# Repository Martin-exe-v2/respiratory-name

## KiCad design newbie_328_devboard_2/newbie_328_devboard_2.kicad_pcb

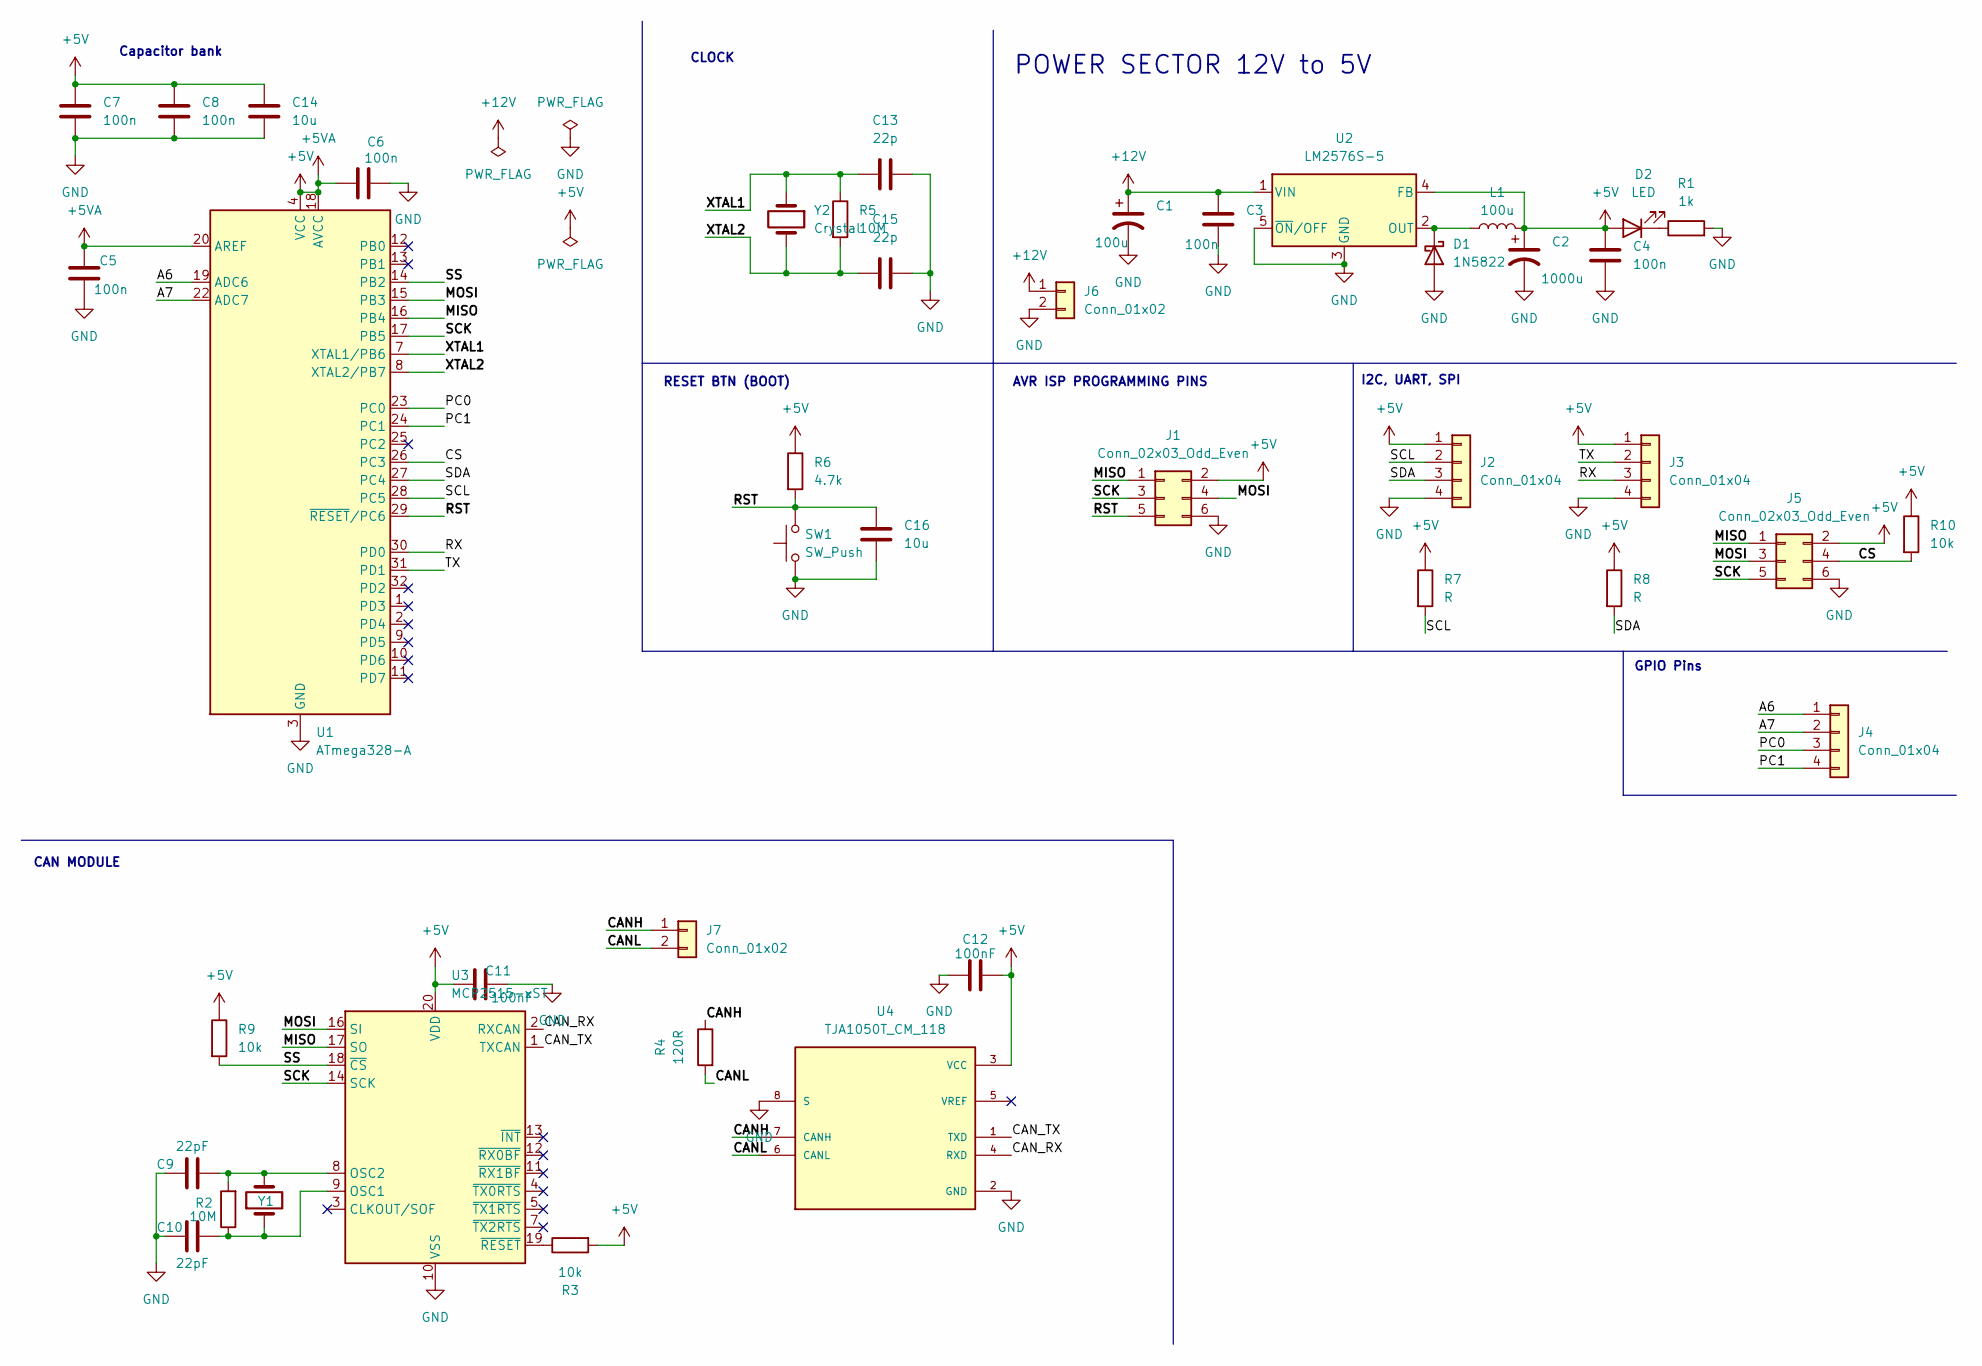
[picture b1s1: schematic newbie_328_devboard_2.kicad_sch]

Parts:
C1: 100u; CP_Radial_D10.0mm_P2.50mm
C2: 1000u; CP_Radial_D10.0mm_P2.50mm
C3, C4, C5, C6, C7, C8: 100n; C_0805_2012Metric_Pad1.18x1.45mm_HandSolder
C9, C10: 22pF; C_0805_2012Metric_Pad1.18x1.45mm_HandSolder
C11, C12: 100nF; C_0805_2012Metric_Pad1.18x1.45mm_HandSolder
C13, C15: 22p; C_0805_2012Metric_Pad1.18x1.45mm_HandSolder
C14, C16: 10u; C_0805_2012Metric_Pad1.18x1.45mm_HandSolder
D1: 1N5822; D_DO-201AD_P15.24mm_Horizontal
D2: LED; LED_0805_2012Metric_Pad1.15x1.40mm_HandSolder
J1, J5: Conn_02x03_Odd_Even; PinHeader_2x03_P2.54mm_Vertical
J2, J3, J4: Conn_01x04; PinHeader_1x04_P2.54mm_Vertical
J6, J7: Conn_01x02; PinHeader_1x02_P2.54mm_Vertical
L1: 100u; L_10.4x10.4_H4.8
R1: 1k; R_0805_2012Metric_Pad1.20x1.40mm_HandSolder
R2, R5: 10M; R_0805_2012Metric_Pad1.20x1.40mm_HandSolder
R3, R9, R10: 10k; R_0805_2012Metric_Pad1.20x1.40mm_HandSolder
R4: 120R; R_0805_2012Metric_Pad1.20x1.40mm_HandSolder
R6: 4.7k; R_0805_2012Metric_Pad1.20x1.40mm_HandSolder
R7, R8: R; R_0805_2012Metric_Pad1.20x1.40mm_HandSolder
SW1: SW_Push; SW_PUSH_6mm
U1: ATmega328-A; TQFP-32_7x7mm_P0.8mm
U2: LM2576S-5; TO-263-5_TabPin3
U3: MCP2515-xST; TSSOP-20_4.4x6.5mm_P0.65mm
U4: TJA1050T_CM_118; SOIC127P600X175-8N; PARTREV 4
Y1: 20MHz; Crystal_HC49-U_Vertical
Y2: Crystal; Crystal_HC49-U_Vertical

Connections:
+5V: C2.1, C4.1, C5.1, C6.1, C7.2, C8.2, C11.2, C12.2, C14.2, D2.2 (A), J1.2, J2.1, J3.1, J5.2, L1.2, R3.2, R6.1, R7.1, R8.1, R9.1, R10.1, U1.4 (VCC), U1.6 (VCC), U1.18 (AVCC), U1.20 (AREF), U2.4 (FB), U3.20 (VDD), U4.3 (VCC)
+12V: C1.1, C3.1, J6.1, U2.1 (VIN)
/A6: J4.1, U1.19 (ADC6)
/A7: J4.2, U1.22 (ADC7)
/CANH: J7.1, R4.1, U4.7 (CANH)
/CANL: J7.2, R4.2, U4.6 (CANL)
/CAN_RX: U3.2 (RXCAN), U4.4 (RXD)
/CAN_TX: U3.1 (TXCAN), U4.1 (TXD)
/CS: J5.4, R10.2, U1.26 (PC3)
/MISO: J1.1, J5.1, U1.16 (PB4), U3.17 (SO)
/MOSI: J1.4, J5.3, U1.15 (PB3), U3.16 (SI)
/PC0: J4.3, U1.23 (PC0)
/PC1: J4.4, U1.24 (PC1)
/RST: C16.1, J1.5, R6.2, SW1.2, U1.29 (~RESET/PC6)
/RX: J3.3, U1.30 (PD0)
/SCK: J1.3, J5.5, U1.17 (PB5), U3.14 (SCK)
/SCL: J2.2, R7.2, U1.28 (PC5)
/SDA: J2.3, R8.2, U1.27 (PC4)
/SS: R9.2, U1.14 (PB2), U3.18 (~CS)
/TX: J3.2, U1.31 (PD1)
/XTAL1: C13.1, R5.1, U1.7 (XTAL1/PB6), Y2.1
/XTAL2: C15.1, R5.2, U1.8 (XTAL2/PB7), Y2.2
GND: C1.2, C2.2, C3.2, C4.2, C5.2, C6.2, C7.1, C8.1, C9.1, C10.1, C11.1, C12.1, C13.2, C14.1, C15.2, C16.2, D1.2 (A), J1.6, J2.4, J3.4, J5.6, J6.2, R1.2, SW1.1, U1.3 (GND), U1.5 (GND), U1.21 (GND), U2.3 (GND), U2.5 (~ON/OFF), U3.10 (VSS), U4.2 (GND), U4.8 (S)
unnamed: D1.1 (K), L1.1, U2.2 (OUT)
unnamed: D2.1 (K), R1.1
unnamed: C10.2, R2.1, U3.9 (OSC1), Y1.1
unnamed: C9.2, R2.2, U3.8 (OSC2), Y1.2
unnamed: R3.1, U3.19 (~RESET)

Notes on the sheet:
POWER SECTOR 12V to 5V
Capacitor bank
RESET BTN (BOOT)
AVR ISP PROGRAMMING PINS
I2C, UART, SPI
CLOCK
CAN MODULE
GPIO Pins

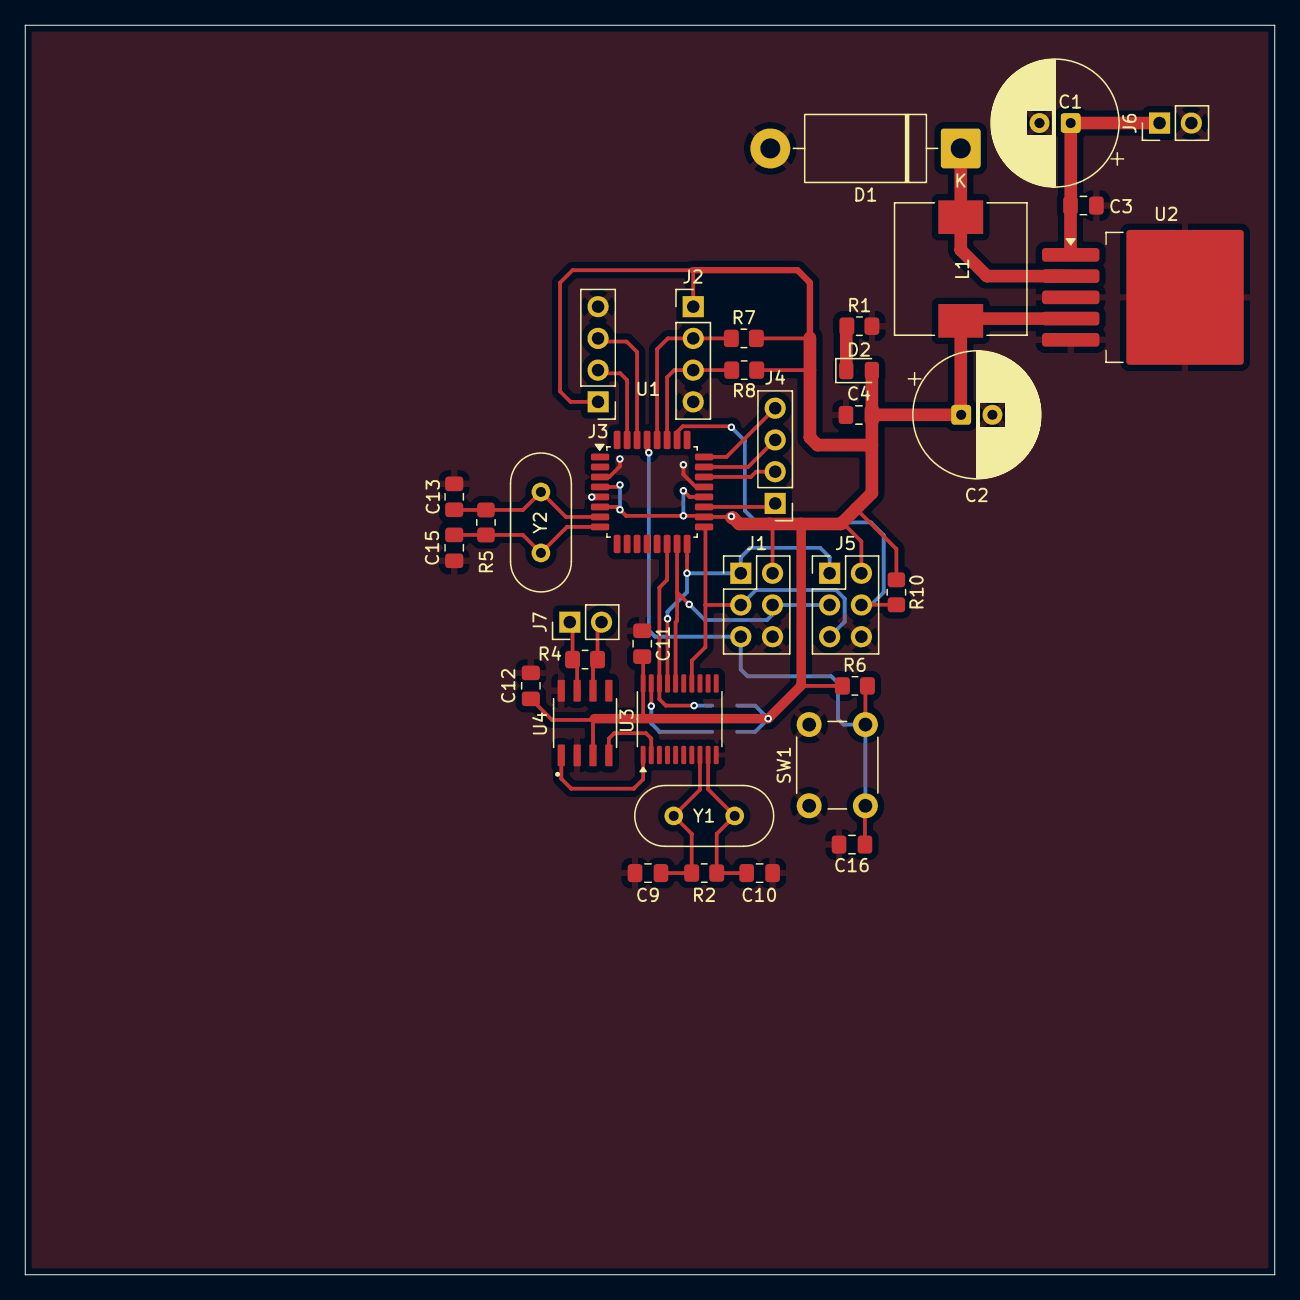
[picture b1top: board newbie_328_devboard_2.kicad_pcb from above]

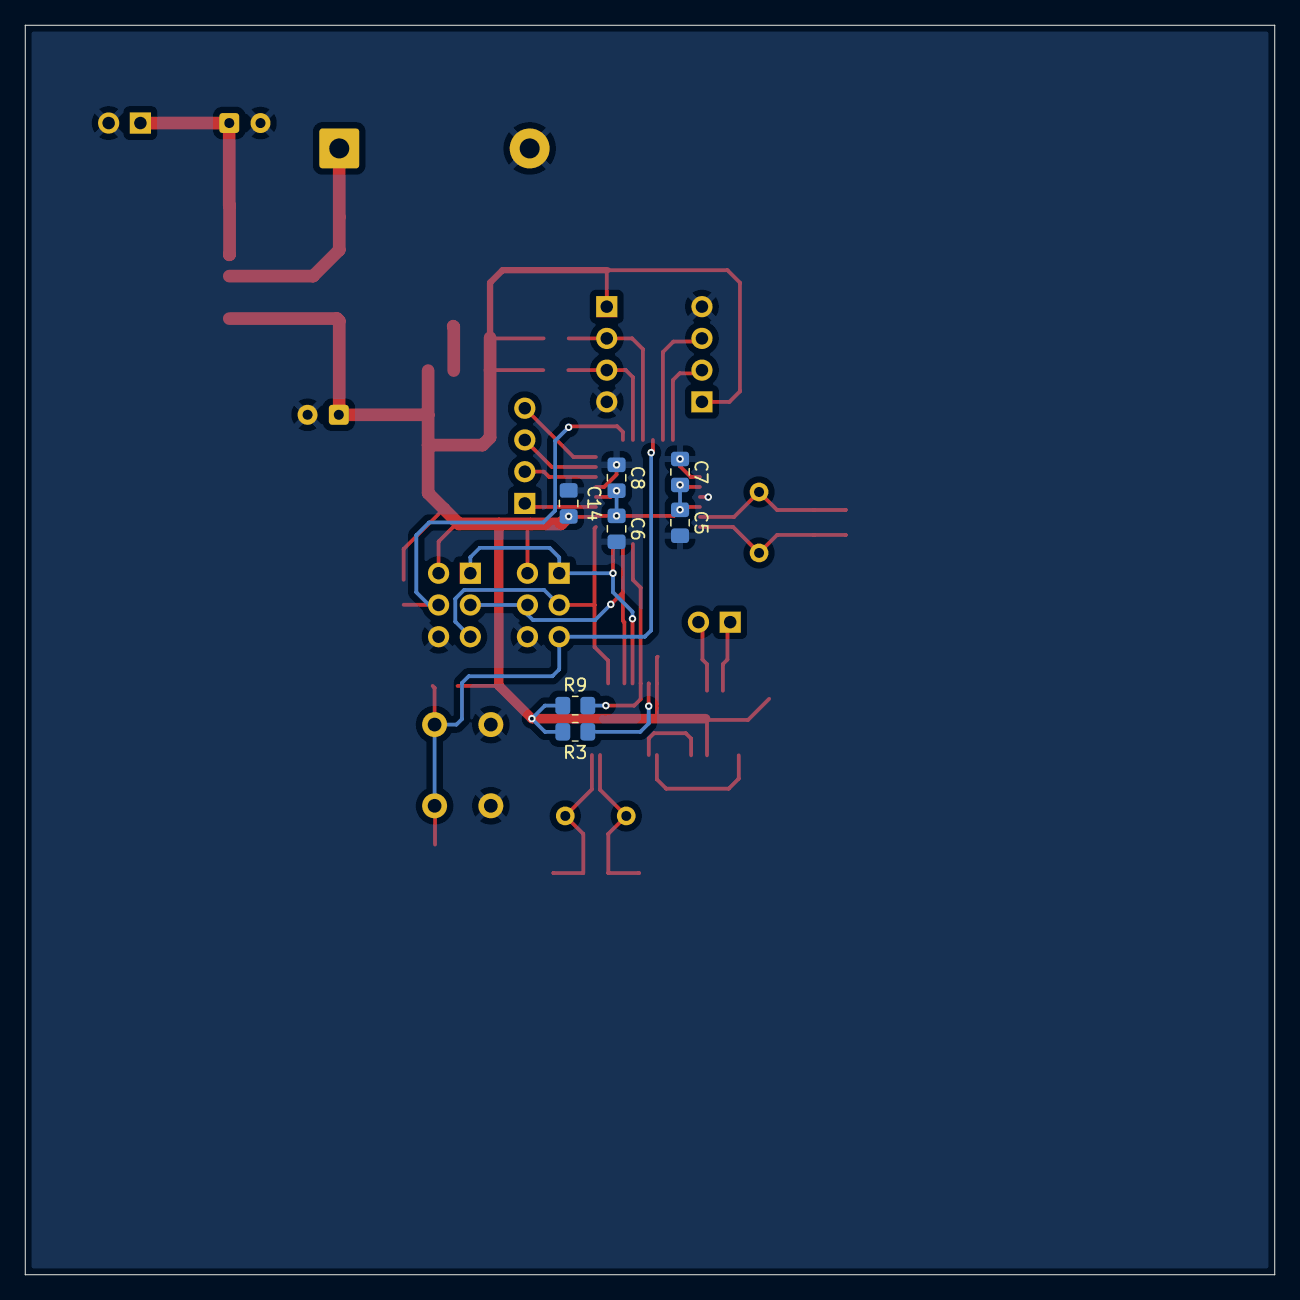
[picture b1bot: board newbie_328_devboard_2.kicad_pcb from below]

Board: 2 copper layers, 100.0 x 100.0 mm, 43 parts (7 on the bottom side), 28 nets.

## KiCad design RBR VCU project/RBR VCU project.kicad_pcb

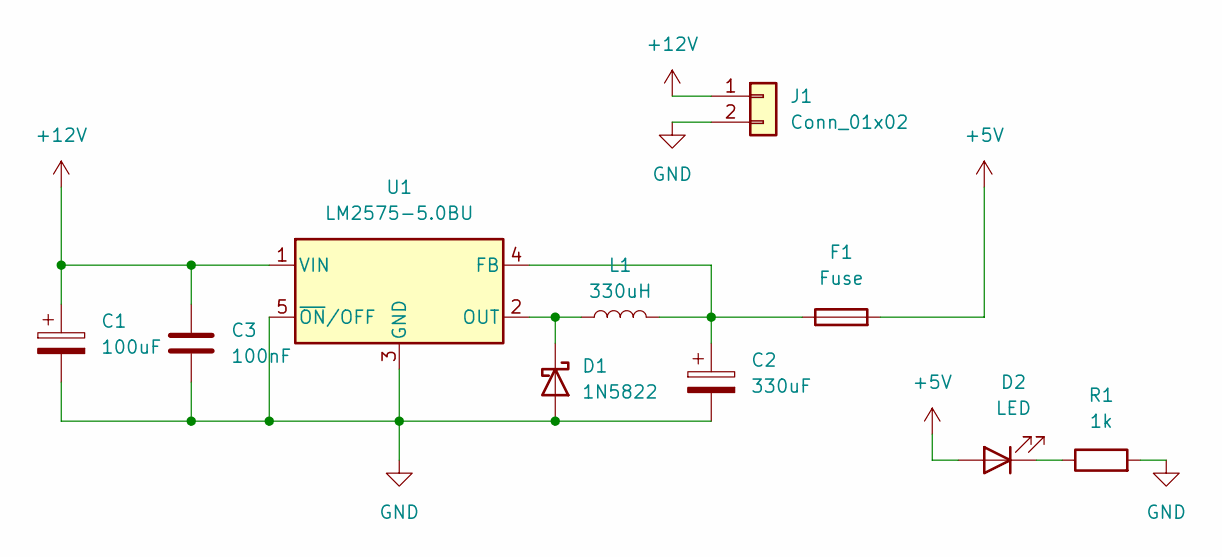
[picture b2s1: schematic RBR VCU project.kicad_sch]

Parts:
C1: 100uF; CP_Radial_D6.3mm_P2.50mm
C2: 330uF; CP_Radial_D6.3mm_P2.50mm
C3: 100nF; C_0805_2012Metric_Pad1.18x1.45mm_HandSolder
D1: 1N5822; D_DO-201AD_P15.24mm_Horizontal
D2: LED; D_0805_2012Metric_Pad1.15x1.40mm_HandSolder
F1: Fuse; Fuse_0805_2012Metric_Pad1.15x1.40mm_HandSolder
J1: Conn_01x02; JST_XH_B2B-XH-A_1x02_P2.50mm_Vertical
L1: 330uH; L_Neosid_SM-NE127_HandSoldering
R1: 1k; R_0805_2012Metric_Pad1.20x1.40mm_HandSolder
U1: LM2575-5.0BU; TO-263-5_TabPin3

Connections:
+5V: D2.2 (A), F1.2
+12V: C1.1, C3.1, J1.1, U1.1 (VIN)
GND: C1.2, C2.2, C3.2, D1.2 (A), J1.2, R1.2, U1.3 (GND), U1.5 (~ON/OFF)
unnamed: D1.1 (K), L1.1, U1.2 (OUT)
unnamed: D2.1 (K), R1.1
unnamed: C2.1, F1.1, L1.2, U1.4 (FB)

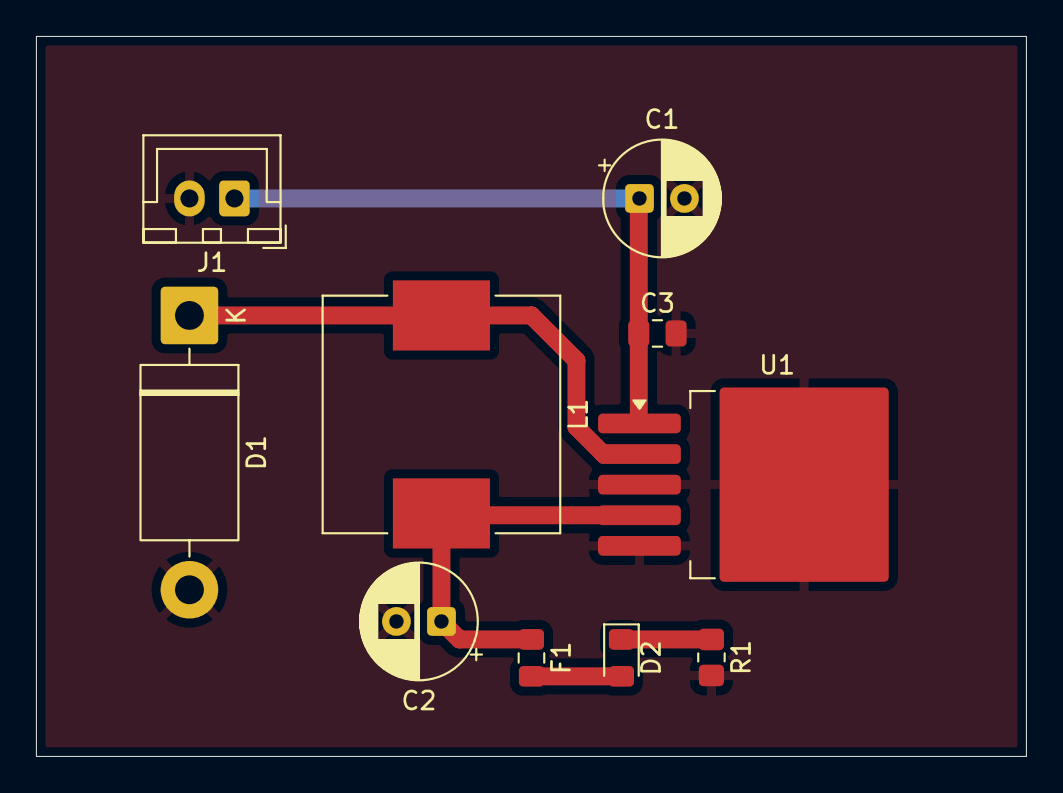
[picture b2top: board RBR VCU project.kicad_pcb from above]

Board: 2 copper layers, 55.0 x 40.0 mm, 10 parts (0 on the bottom side), 6 nets.

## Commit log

2025-09-25 The homework
    moved the files by ctrl C+V in finder
2025-10-19 Grouped HW by folder
2025-10-19 Did the homework
2025-11-15 q1 done
2025-11-16 Added a missing type cast
2025-12-01 Added VCU project
2025-12-01 Added old stuff, removed redundant kicad folder
2025-12-01 cache
2025-12-01 project
2026-01-09 minor edits to PCB
2026-01-09 Second iteration of PCB
